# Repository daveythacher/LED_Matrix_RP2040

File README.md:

# LED_Matrix_RP2040
Hardware module for abstracting LED matrix interface. Raw data is sent over an IO bus which is then replayed to the LED matrix repeatedly. Application logic is responsible for producing raw data and generating synchronization signal.

## Status
This code base is a work in progress. See [this](https://github.com/daveythacher/LED_Matrix_RP2040/blob/main/LED_Matrix/README.md#status) for more details.

This code basis will likely be abandoned due to integrity issues. Most LED Matrix libraries have issues with integrity. I have been on an adventure trying to improve the quality of LED Matrix displays, which is quite poor in my opinion. Only some of my findings have been documented and at some point I will just have to be comfortable with the journey's merit. (I trust my verbage finds you even better.) My personal growth from this has been a unique perspective on reality, which was certainly worth my time.

Roadblock: [Issue Number 61](https://github.com/daveythacher/LED_Matrix_RP2040/issues/61)

I assume no liability in any way as a result of this code base. This code base is [licensed under GPL 3](https://github.com/daveythacher/LED_Matrix_RP2040/blob/main/LICENSE).

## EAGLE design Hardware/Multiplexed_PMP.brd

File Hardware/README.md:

Most of these are prototypes and have defects. Use them as references for concepts only. Use at your own risk.

## Interface board
Files used are Interface.sch (Eagle schematic file) and Interface.brd (Eagle board file).

This board implements basic serial_uart or uart serial algorithm. Uses full duplex RS-485 transceiver capable of 10 Mbits per second. However RP2040 only supports up to 7.8 Mbits per second. 

Board is designed to fit to the back of panel. Differential UART is used to improve signal immunity from cross talk, single ended problems (power surges, distance, etc.), EMI, etc. However not all of this may be implemented correctly. Exact distance limits are not known, but cables are kept short enough to remove chances of this being a significant issue. Ethernet cable is uses for cost purposes and is not interoperable with Ethernet specifications. Uses standard straight through Ethernet cable pinning. (Be mindful of certain Ethernet jacks/jack adapters pinout.)

Board has additional features like a reset button which help with reprogramming the chip. It also uses the RPI PICO's voltage regulator to power the board. Currently power is feed over Ethernet cable up to 5 volts. The load of the RP2040 is not believed to cause a significant issue. PICO voltage regulator is capable of step up and step down. Current on the Ethernet cable is kept low to avoid losses. Power and ground are kept on their own pairs intentionally, as is TX and RX.

### Known defects in Interface
In Interface.brd the differential signals are not routed correctly.

The HUB75 connector is assumed to work with LED Panels modified to work with a power rail at 3.3 volts. It is not recommended to use with 5 volt panels unless known to be supported. 

There is no reverse polarity protection. If wired incorrectly damage to components can occur.

Do not plug into Ethernet switches or other Ethernet hardware, this is not supported or allowed. RS-485 plus power is passed over Ethernet.

There is no termination for transmission lines or long ribbon cables. This is intended to connect directly to the panel without ribbon cable.

Fan out performance determines the clock speed of many panels which can be less than 25MHz. This is from the panel itself. There is no buffers used as most panels have buffers near inputs. Long chains will have issues with ribbon cable jumper and fan out. (This can be corrected in some cases via special jumper cables, which is outside the scope of this project.)

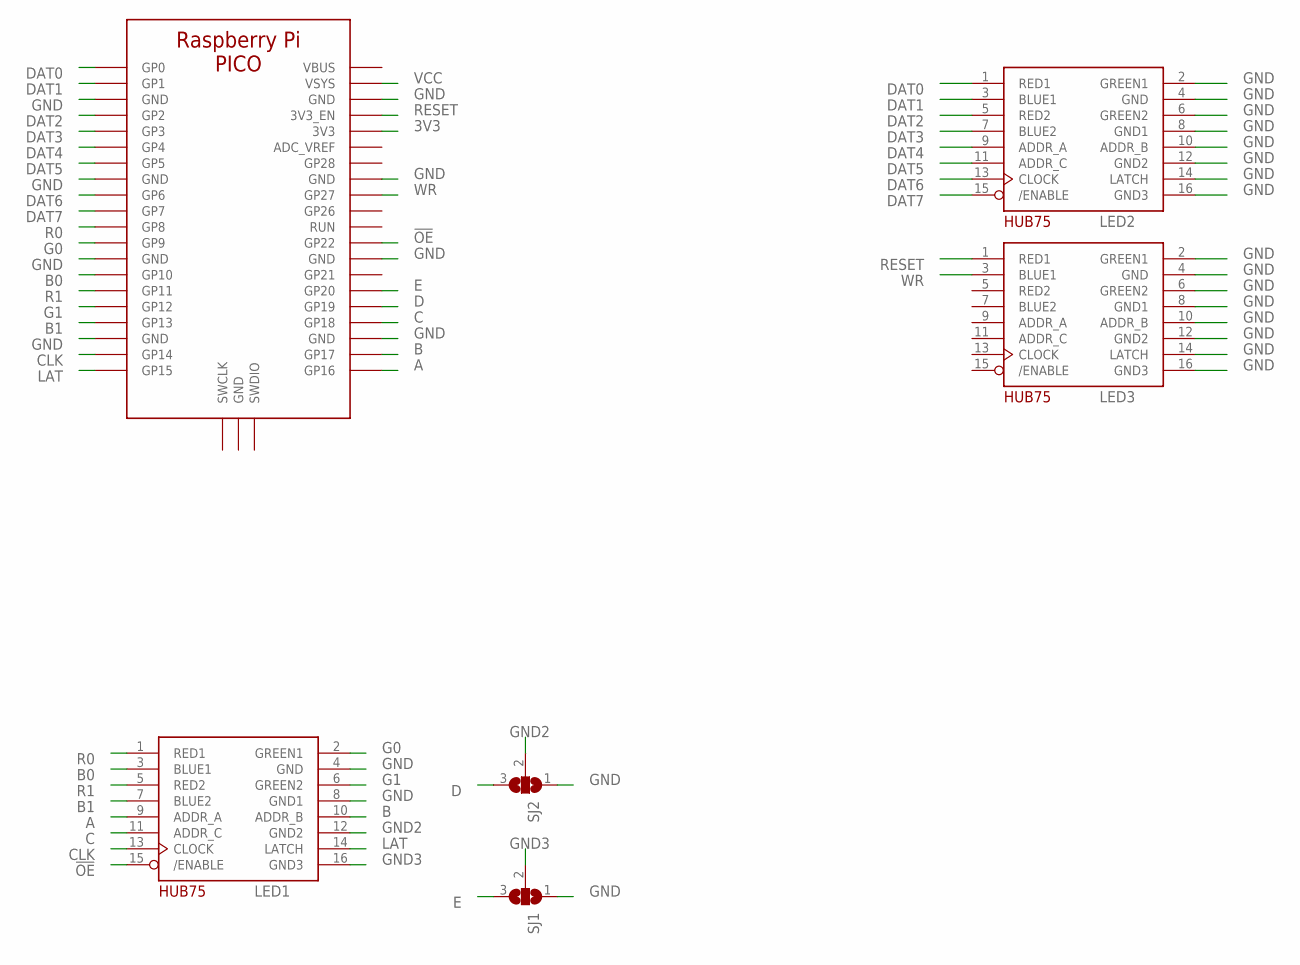
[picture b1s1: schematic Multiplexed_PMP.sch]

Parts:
LED1, LED2, LED3: HUB75MATRIX; 2X08-IDC
SJ1, SJ2: SJ2W; SJ_2
U$1: PICO

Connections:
3V3: U$1.P$3V3 (3V3)
!OE: LED1.15 (/ENABLE), U$1.P$GP22 (GP22)
A: LED1.9 (ADDR_A), U$1.P$GP16 (GP16)
ADC_VREF: U$1.P$ADC_VREF (ADC_VREF)
B: LED1.10 (ADDR_B), U$1.P$GP17 (GP17)
B0: LED1.3 (BLUE1), U$1.P$GP10 (GP10)
B1: LED1.7 (BLUE2), U$1.P$GP13 (GP13)
C: LED1.11 (ADDR_C), U$1.P$GP18 (GP18)
CLK: LED1.13 (CLOCK), U$1.P$GP14 (GP14)
D: SJ2.3, U$1.P$GP19 (GP19)
DAT0: LED2.1 (RED1), U$1.P$GP0 (GP0)
DAT1: LED2.3 (BLUE1), U$1.P$GP1 (GP1)
DAT2: LED2.5 (RED2), U$1.P$GP2 (GP2)
DAT3: LED2.7 (BLUE2), U$1.P$GP3 (GP3)
DAT4: LED2.9 (ADDR_A), U$1.P$GP4 (GP4)
DAT5: LED2.11 (ADDR_C), U$1.P$GP5 (GP5)
DAT6: LED2.13 (CLOCK), U$1.P$GP6 (GP6)
DAT7: LED2.15 (/ENABLE), U$1.P$GP7 (GP7)
E: SJ1.3, U$1.P$GP20 (GP20)
G0: LED1.2 (GREEN1), U$1.P$GP9 (GP9)
G1: LED1.6 (GREEN2), U$1.P$GP12 (GP12)
GND: LED1.4 (GND), LED1.8 (GND1), LED2.2 (GREEN1), LED2.4 (GND), LED2.6 (GREEN2), LED2.8 (GND1), LED2.10 (ADDR_B), LED2.12 (GND2), LED2.14 (LATCH), LED2.16 (GND3), LED3.2 (GREEN1), LED3.4 (GND), LED3.6 (GREEN2), LED3.8 (GND1), LED3.10 (ADDR_B), LED3.12 (GND2), LED3.14 (LATCH), LED3.16 (GND3), SJ1.1, SJ2.1, U$1.P$GND (GND), U$1.P$GND3 (GND), U$1.P$GND8 (GND), U$1.P$GND13 (GND), U$1.P$GND18 (GND), U$1.P$GND23 (GND), U$1.P$GND28 (GND), U$1.P$GND33 (GND), U$1.P$GND38 (GND)
GND2: LED1.12 (GND2), SJ2.2
GND3: LED1.16 (GND3), SJ1.2
LAT: LED1.14 (LATCH), U$1.P$GP15 (GP15)
R0: LED1.1 (RED1), U$1.P$GP8 (GP8)
R1: LED1.5 (RED2), U$1.P$GP11 (GP11)
RESET: LED3.1 (RED1), U$1.P$3V3_EN (3V3_EN)
VBUS: U$1.P$VBUS (VBUS)
VCC: U$1.P$VSYNC (VSYS)
WR: LED3.3 (BLUE1), U$1.P$GP27 (GP27)

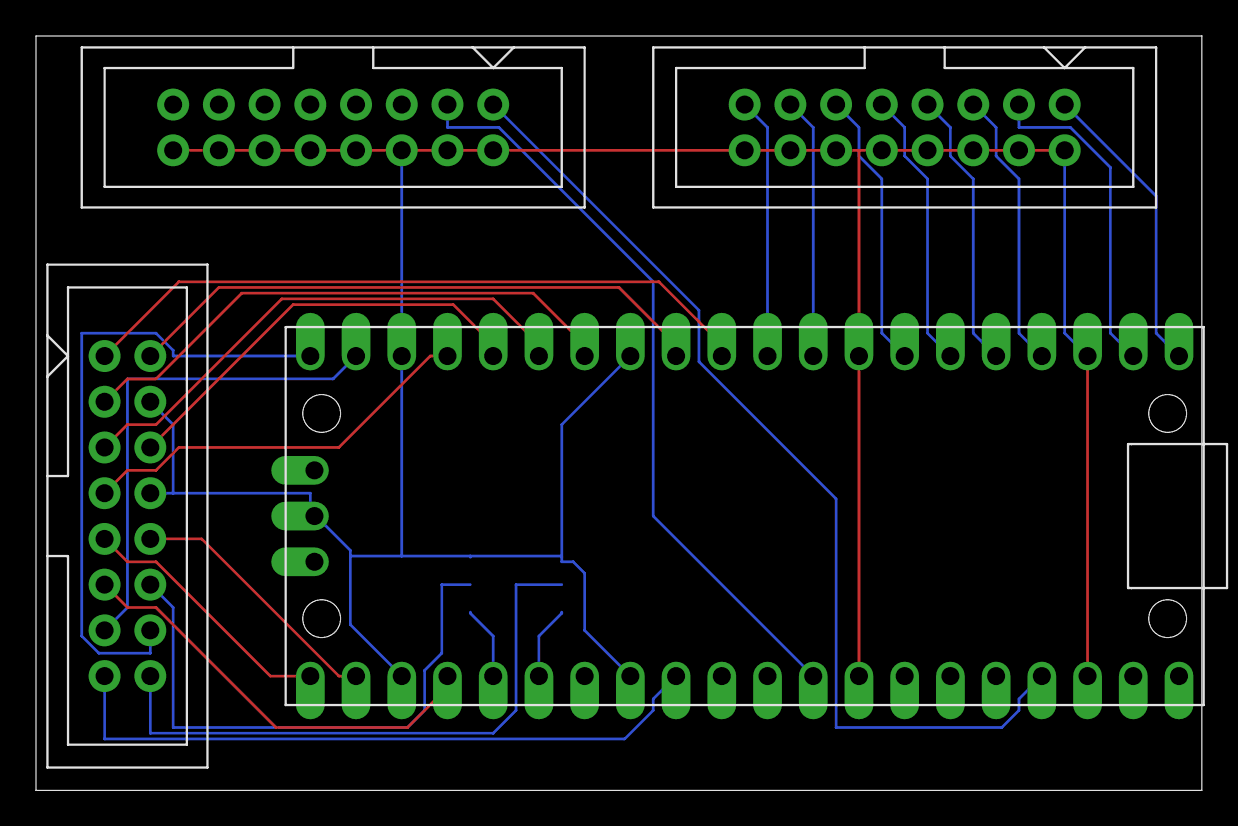
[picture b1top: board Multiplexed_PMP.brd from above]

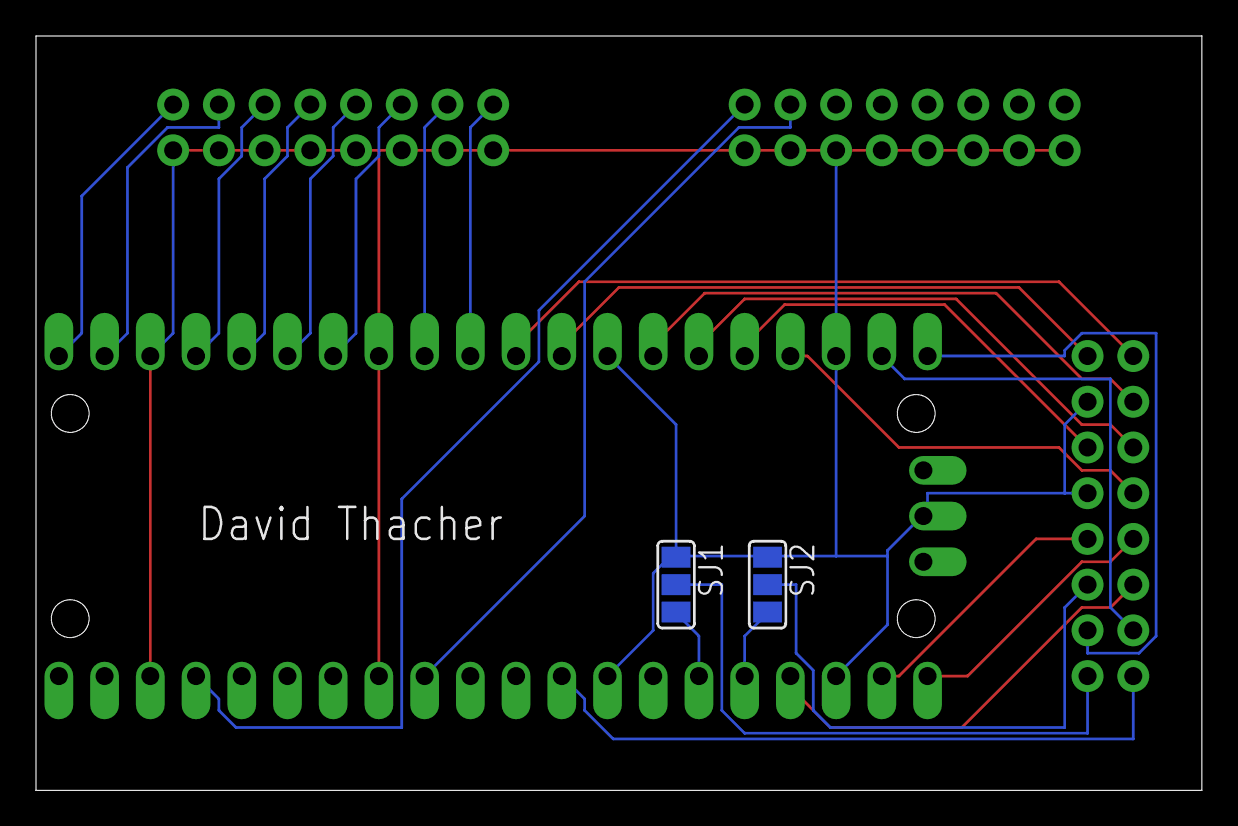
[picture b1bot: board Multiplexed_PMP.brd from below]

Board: 2 copper layers, 64.8 x 41.9 mm, 6 parts (2 on the bottom side), 27 nets.

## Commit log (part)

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2024-05-13 Work in progress for query support.
2024-05-13 Make it compile
2024-06-12 Removing pointer cast
2024-06-27 speed things up a little
2024-07-11 Adding comments about error
2024-07-11 Comments about addressing
2024-07-18 Adding small SIMD logic for LUT. Not linked in yet, and does not do much right now. More of a place holder for rewriting things to be more clear.
2024-07-18 This should have been in the first draft
2024-07-19 Rewrite with SIMD
2024-07-22 Making TCAM use SIMD, WIP
2024-07-28 update CMake release build
2024-08-20 Starting refactor of Protocol
2024-08-20 Split SIMD implementations
2024-08-20 Starting refactor of Node Serial UART
2024-08-20 Refactoring Node Serial UART
2024-08-20 Updating preprocessor macros for headers
2024-08-20 Updating dependencies
2024-08-20 Updating CMake options
2024-08-20 Refactoring Serial Node and Protocol
2024-08-20 Forgot to remove this file
2024-08-21 Refactoring Serial Protocol and Node
2024-08-21 Hiding internal details
2024-08-23 Some progress on Refactor
2024-08-23 Removing file
2024-09-10 Adding checksum for commands
2024-09-10 Fixing state machine
2024-09-10 Documentation for state machine
2024-09-16 Small changes for using DMA in loop
2024-09-16 Found a race condition which requires even more memory usage to fix
2024-10-27 Reducing load times. Not finished. Only worked on PWM algorithm. Still need to do BCM.
2024-10-27 Add null line to calculator. This is used for ghosting prevention aka connecting the dots.
2024-10-27 reduce the ram even more
2024-11-03 Updates for BCM. Still both BCM and PWM are missing VSYNC function
2024-11-03 Trying to clarify a comment
2024-11-03 I actually already did vsync
2024-11-03 Outline for TCAM refactor
2024-11-03 Incomplete TCAM refactor
2024-11-04 Help smooth out the access time. There is nothing we can do for DMA really. (Capacity vs arbiter size) We can possibly increase the CPU performance with block RAM.
2024-11-04 Clarify what has happened to DMA bandwidth and response time. Banking would potentially improve this, as multiplexing is a trap. This will lead to capacity loss.
2024-11-04 removing picotool as bootloader
2024-11-04 Moving things to XIP cache
2024-11-13 Removing last friend
2024-11-17 Standardize types
2024-11-19 Allow remotely computed buffers. (Not recommended)
2024-11-20 Hiding preprocessor macros
2024-11-22 Future automation
2024-11-25 Reworking PIO program to use more readable format. The performance and resource usage is not ideal, but for this it should work just fine. Also move CMake dependencies around.
2024-11-25 Beginning RTOS refactor. Moving away from ISR logic to polling logic. Adding automation which will increase memory consumption slightly.
2024-11-26 Holding back on RTOS for now. (Was considering a port to Teensy 4.) Still planning automation.
2024-11-26 Making IRQ clear automatically at join.
2024-11-27 Adding delay to PIO
2024-11-27 Adding comments
2024-12-03 Create sub folder for PIO program
2024-12-03 Updating namespace name
2024-12-03 Adding wrappers for DMA and PIO SM.
2024-12-04 Adding GPIO claim function
2024-12-04 Adding GPIO claim to Serial Protocol
2024-12-04 Adding RTOS
2024-12-04 Integrating FreeRTOS into build system
2024-12-04 Messing around
2024-12-07 Removing interrupts
2024-12-08 Switching to dynamic memory for the fun of it
2024-12-09 Adding queue
2024-12-09 Moving to HEAP3 to force SDK malloc to be used by all
2024-12-09 Adding yield
2024-12-11 Serial is completely garbage. Still working on Matrix::Buffer and Matrix::Packet. Still working on templates. Still working on DMA, Multiplex, PIO::SM, Matrix::Multiplex, Matrix::Matrix::, Matrix::Wo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
2024-12-19 Allow for the backend to pass up the type/order. So the frontend never needs to care.
2024-12-20 Adding PWM_Buffer
2024-12-20 Comments
2024-12-20 Splitting DMA header into multiple files
2024-12-20 Splitting headers into multiple files
2024-12-20 Messing with CMake
2024-12-20 Adding factory for future usage
2024-12-25 Adding summary of porting
2024-12-27 Documentation
2025-01-05 Allowing both cores to be used for computation. TODO: Add buffered IO to serial protocol.
2025-01-05 Fixing race condition, but I am not sure it works on RP2040.
2025-01-19 Reworking FreeRTOS CMake
2025-01-19 removing low refresh support aka BCM
2025-01-20 Revert "removing low refresh support aka BCM"
    This reverts commit ced7cd2aab0690c4f8e805a0746717a8efb49ea1.
2025-03-09 DMA as service under its own cluster
2025-03-10 Working on Serial Protocol. Not finished, still needs work.
2025-03-11 Frame thing for out of order
2025-03-11 Bug fixes
2025-03-21 Syncing work in progress. Adding wrapper for PWM_Worker to allow different implementations. Dot product in some hardware configuration may be faster than LUTversion. For RP2040 LUT version is better.
2025-03-21 typo
2025-03-21 Little bit of a joke
2025-03-21 Removing BCM
2025-03-28 Update harmonics to be at least 10
2025-04-04 adding files
2025-04-04 Adding dot product sample
2025-04-04 Condensing SIMD implementations
2025-04-04 Optimizing performance on Cortex-M0+
2025-04-04 Dot product stuff
2025-04-10 Something ain't right
2025-04-11 #49 Reworking headers for Concurrent::IO::DMA.
2025-04-11 Improve sleep time in Matrix/HUB75/PWM/PWM_Multiplex
2025-04-11 #49 Working on interface of Targets
2025-04-12 #51 Removing files
2025-05-13 Adding watchdog service outline. Still working on channels.
2025-05-13 Adding watchdog logic. Still missing initialization in constructor.
2025-05-14 Removing templates and dynamic configuration from Matrix. Only going to support 8x8 matrix. Consider feature mode to enable channeling the monocolor via pin. Assuming tricolor matrix but only on colo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
2025-05-14 Removing direct and shifter multiplexer, but maintain the precident which allows them to come back
2025-05-14 Saving copy of old PWM Worker LUT approach.
2025-05-14 Saving a copy of old PIO SM approach.
2025-05-14 Saving a copy of DMA and Frame approach.
2025-05-14 Forcing the configuration to preprocessor macros.
2025-05-15 Adding Dot Correction helper
2025-05-15 Continuing migration away from HUB75
2025-05-15 Switching status to embrace threads. Considering removing control notion and forcing host to implement hardware networking front end solution.
2025-05-15 Fixing comments. Fixing waits. Removing control node
2025-05-16 Removing modules which are not likely to be needed as much.
2025-05-17 Keeping HUB75 version
2025-05-19 Bringing back a lot of the old code
2025-05-20 Removing test modules. Removing mono module. Removing PWM_Worker
2025-05-20 Removing DMA wrappers. Using file based port layer. Removing Frame wrappers. Using file based port layer.
2025-05-20 Changing hardware profile to led the colors be decided by the hardware and the high level software. This code is just a universal intermediate which does not care. BUS8 is a new 8-bit bus design whic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
2025-05-24 Making it simpler
2025-05-24 This is the right one to use?
2025-05-28 Removing delete from core1
2025-05-28 Fixing: removing delete from core1
2025-05-28 stuff
2025-05-29 Adding blob for SPWM frame, work in progress.
2025-05-29 WIP: SPWM
2025-05-29 Moving test cases
2025-05-29 Updating Tests
2025-06-02 Having processor flush before DMA operations.
2025-06-02 Adding Serial. Fixing compilation errors
2025-06-02 Forgot to add this.
2025-06-03 Adding Header class which includes TCAM, shift register, vector like compare operations, header builder, etc. Used to splice byte system in command parsers.
2025-06-03 Adding Command interface. This will lay the foundation for the interface between header and commands.
2025-06-03 Removing files from previous implementation attempt/iteration.
2025-06-03 Removing more old files. Moving Command to its proper place. Updating the Command headers and source files. No implementation just yet.
2025-06-03 Updating CMake. Removing old file.
2025-06-03 Adding Command header to allow for matrix data and frame swap.
2025-06-03 Adding comment for future work
2025-06-03 Adding Control command(s) and Power command for turning off LED array
2025-06-03 Getting the latest changes to LED Panel Settings Calculator Script
2025-06-03 Filling in filters. Making filter length programmable. No longer a power of 2 in length. RP2040 does not care but SIMD capable hardware probably would.
2025-06-03 Adding checksum.
2025-06-04 Adding checksum logic. Implementing CMake logic for CRC32. Adding virtual methods to commands, without implementation.
2025-06-04 Add intermediate header parsing to Data command. Adding swap command.
2025-06-04 Add payload section to Data command
2025-06-04 Adding nonblocking version of Node operators. This is not completely right, but should do for now.
2025-06-04 Getting size command to work, with a hack
2025-06-04 Fixing CMake Hack
2025-06-04 Adding swap command's implementation.
2025-06-04 Removing old ID command.
2025-06-04 Adding most of power command.
2025-06-04 Adding Test command's implementation.
2025-06-04 Adding connection to power command and matrix implementation(s).
2025-06-04 Adding documentation for application processor
2025-06-04 Removing GPIO claim
2025-06-04 Removing old comments
2025-06-04 Updating documentation
2025-06-05 Removing refresh sychnronization.
2025-06-06 Deleting SPWM
2025-06-07 Updating LED Panel Setting Calculator
2025-06-09 Adding dirty wrapper for dirty C API. Removing hardware FIFO to ensure smooth operation with watchdog.
2025-06-10 Adding reboot command. Adding logic for power command. Adding commands to TCAM.
2025-06-10 Adding files for reboot command.
2025-06-14 Removing HUB75 configuration
2025-06-14 Delete .github/workflows directory
    Workflows require cross compiler.
2025-06-17 Update cmake-single-platform.yml
    This is annoying.
2025-06-17 Update cmake-single-platform.yml
    Avoid it if we can.
2025-06-23 updating script
2026-02-08 Update README with project integrity concerns
    Added personal reflections on the project's integrity issues and development journey.
